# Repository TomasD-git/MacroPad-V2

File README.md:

# MacroPad-V2

A compact 16-key macro pad with rotary encoder and built-in battery — powered by ESP32, fully wireless.  

## Features

- 16 Programmable Keys  
- Rotary Encoder  
- Battery Powered  
- ESP32 with bluetooth  

## How It Works

The MacroPad-V2 uses a seeed xiao ESP32 S3 to manage key matrix and rotary encoder.  

Power is managed by a charging module.  

Firmware handles Bluetooth. The case is 3D printed, with space for the PCB, battery, keys and encoder.  

<details>
  <summary>Pictures</summary>

</details>

<details>
<summary>BOM</summary>

| Name | Purpose | Quantity | Total Cost (USD) | Link | Distributor |
|------|--------|----------|------------------|------|-------------|
| PCB | How would i even make it without PCB | 1 | 11.34 | https://jlcpcb.com | jlcpcb |
| Pin header 2.54mm | soldered onto the pcb then on top of that is the esp32(so it can be visible), the rotary encoder needs this as well | 1 | 3.08 | https://www.aliexpress.com/item/4000873858801.html | Aliepress |
| 1N4148W T4 SOD-123(Diode) | needed in switch matrix(prevents ghosting) | 1 | 2.16 | https://www.aliexpress.com/item/1005010653199938.html | Aliexpress |
| Seeed xiao ESP32 S3 | brain of everything, needed to power use and control all switches and rotary encoder | 1 | 9.06 | https://www.aliexpress.com/item/1005007341749305.html | Aliepress |
| M4 screws 20pcs, 8mm | screwed into heatset inserts to hold case and pcb together | 1 | 2.16 | https://www.aliexpress.com/item/32810872544.html | Aliexpress |
| Heatset inserts, M4 (OD5mm) 30pcs, Length 3mm | Will be melted into the 3D printed case and screws will be inserted into it to hold the case together | 1 | 2.43 | https://www.aliexpress.com/item/1005008666672949.html | Aliexpress |
| Battery holder | Holds battery in place | 1 | 1.84 | https://www.aliexpress.com/item/1005006783038553.html | Aliexpress |
| Battery | to store electricity and later power the esp32 | 1 | 8.85 | https://www.aliexpress.com/item/32810182330.html | Aliexpress |
| Slide switch | shut power to esp32 so it wont consume electricity when not used | 1 | 1.8 | https://www.aliexpress.com/item/1005005633418066.html | Aliexpress |
| Charging module | safely power esp32 and charge battery | 1 | 2.0 | https://www.aliexpress.com/item/1005007176376691.html | Aliexpress |
| Key switches | To use the macropad, (Self sourced) | 1 | 0.0 | https://www.aliexpress.com/item/1005007666734237.html | Aliexpress |
| Rotary encoder | is a part on the pcb | 1 | 1.47 | https://www.aliexpress.com/item/1005009040530746.html | Aliexpress |

</details>

<details>
  <summary>License</summary>

### MIT License

**Copyright (c) [2026] [TomasD-git]**

Permission is hereby granted, free of charge, to any person obtaining a copy
of this software and associated documentation files (the "Software"), to deal
in the Software without restriction, including without limitation the rights
to use, copy, modify, merge, publish, distribute, sublicense, and/or sell
copies of the Software, and to permit persons to whom the Software is
furnished to do so, subject to the following conditions:

The above copyright notice and this permission notice shall be included in all
copies or substantial portions of the Software.

THE SOFTWARE IS PROVIDED "AS IS", WITHOUT WARRANTY OF ANY KIND, EXPRESS OR
IMPLIED, INCLUDING BUT NOT LIMITED TO THE WARRANTIES OF MERCHANTABILITY,
FITNESS FOR A PARTICULAR PURPOSE AND NONINFRINGEMENT. IN NO EVENT SHALL THE
AUTHORS OR COPYRIGHT HOLDERS BE LIABLE FOR ANY CLAIM, DAMAGES OR OTHER
LIABILITY, WHETHER IN AN ACTION OF CONTRACT, TORT OR OTHERWISE, ARISING FROM,
OUT OF OR IN CONNECTION WITH THE SOFTWARE OR THE USE OR OTHER DEALINGS IN THE
SOFTWARE.

</details>

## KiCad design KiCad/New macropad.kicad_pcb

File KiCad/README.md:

# Here you can find all KiCad related files

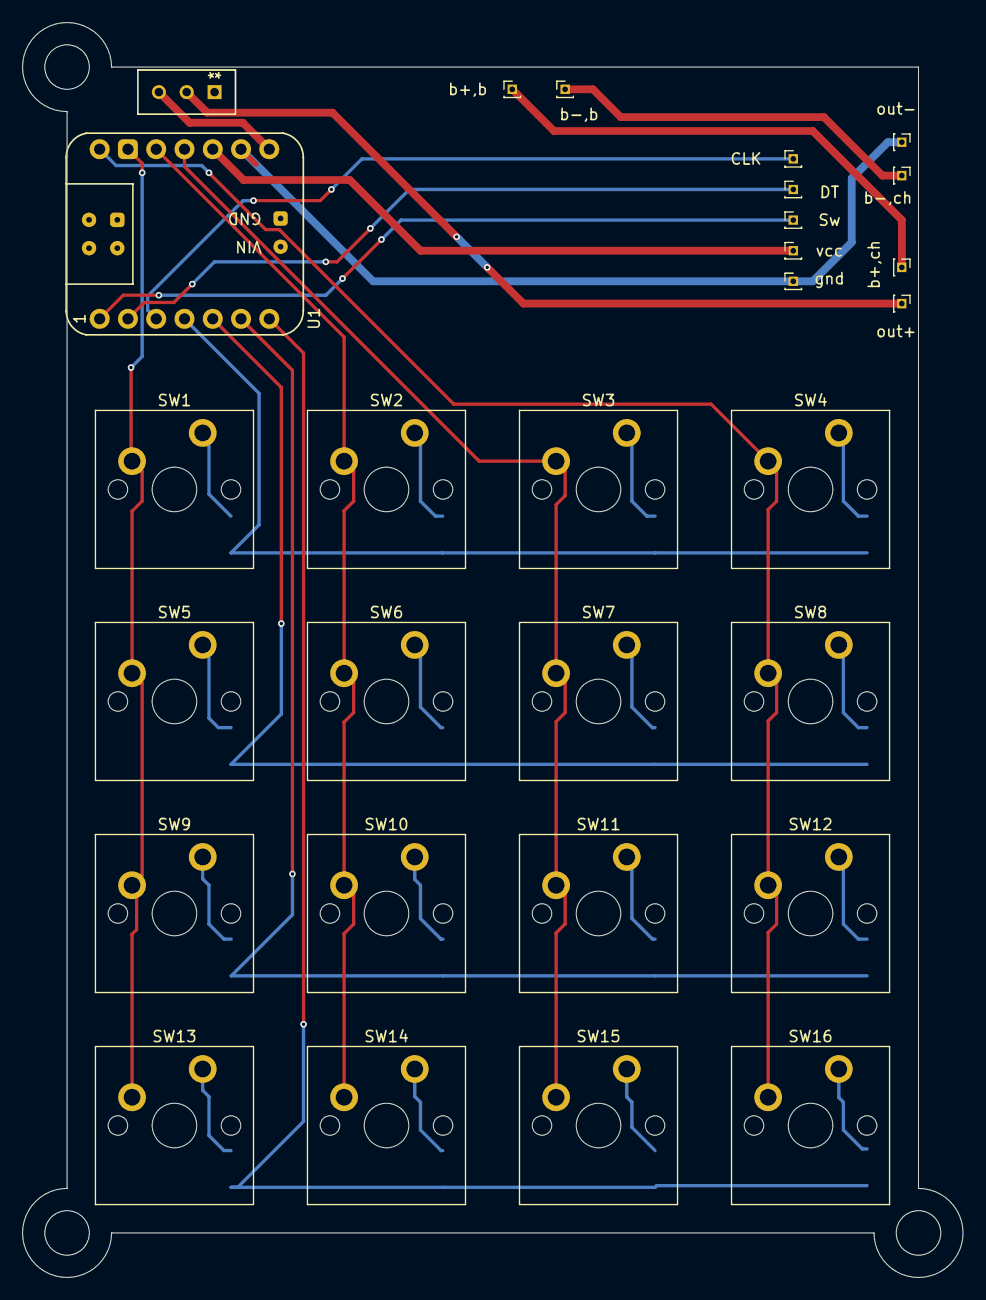
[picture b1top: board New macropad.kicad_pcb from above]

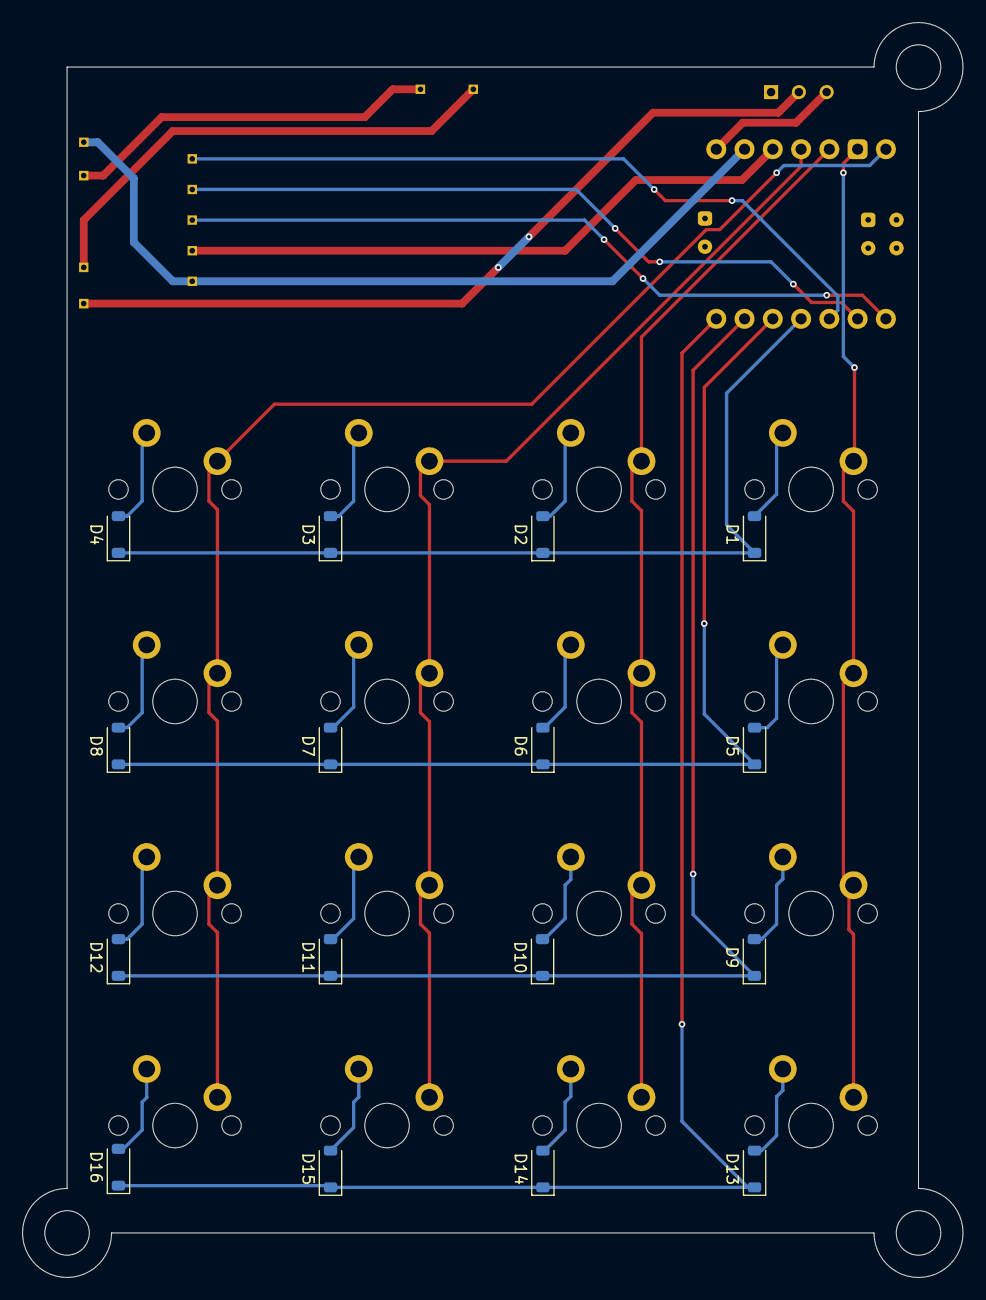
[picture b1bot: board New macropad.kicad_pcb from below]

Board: 2 copper layers, 84.5 x 112.7 mm, 45 parts (16 on the bottom side), 33 nets.

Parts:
CLK: Conn_01x01_Socket; PinHeader_1x01_P1.00mm_Vertical
D1, D2, D3, D4, D5, D6, D7, D8, D9, D10, D11, D12, D13, D14, D15, D16: 1N4148WT; D_SOD-123
DT: Conn_01x01_Socket; PinHeader_1x01_P1.00mm_Vertical
SW1, SW2, SW3, SW4, SW5, SW6, SW7, SW8, SW9, SW10, SW11, SW12, SW13, SW14, SW15, SW16: SW_Push; SW_Cherry_MX_PCB_1.00u
SW17: SS-12D00-G 4 E; 1P2T_SS-12D00_CNK
Sw: Conn_01x01_Socket; PinHeader_1x01_P1.00mm_Vertical
U1: XIAO-ESP32-C3-DIP; Xiao_rp2040_AH_Pogo
b+,b: Conn_01x01_Socket; PinHeader_1x01_P1.00mm_Vertical
b+,ch: Conn_01x01_Socket; PinHeader_1x01_P1.00mm_Vertical
b-,b: Conn_01x01_Socket; PinHeader_1x01_P1.00mm_Vertical
b-,ch: Conn_01x01_Socket; PinHeader_1x01_P1.00mm_Vertical
gnd: Conn_01x01_Socket; PinHeader_1x01_P1.00mm_Vertical
out+: Conn_01x01_Socket; PinHeader_1x01_P1.00mm_Vertical
out-: Conn_01x01_Socket; PinHeader_1x01_P1.00mm_Vertical
vcc: Conn_01x01_Socket; PinHeader_1x01_P1.00mm_Vertical

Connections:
+5V: SW17.3, U1.14 (VBUS)
/Col 1: SW1.1, SW5.1, SW9.1, SW13.1, U1.9 (GPIO8/D8/SCK)
/Col 2: SW2.1, SW6.1, SW10.1, SW14.1, U1.10 (GPIO9/D9/MISO)
/Col 3: SW3.1, SW7.1, SW11.1, SW15.1, U1.11 (GPIO10/D10/MOSI)
/Col 4: SW4.1, SW8.1, SW12.1, SW16.1, U1.8 (GPIO20/D7/RX)
/Row 1: D1.1 (K), D2.1 (K), D3.1 (K), D4.1 (K), U1.4 (GPIO5/A3/D3)
/Row 2: D5.1 (K), D6.1 (K), D7.1 (K), D8.1 (K), U1.5 (GPIO6/D4/SDA)
/Row 3: D9.1 (K), D10.1 (K), D11.1 (K), D12.1 (K), U1.6 (GPIO7/D5/SCL)
/Row 4: D13.1 (K), D14.1 (K), D15.1 (K), D16.1 (K), U1.7 (GPIO21/D6/TX)
GND: U1.13 (GND), gnd.1, out-.1
unnamed: CLK.1, U1.3 (GPIO4/A2/D2)
unnamed: D1.2 (A), SW1.2
unnamed: D2.2 (A), SW2.2
unnamed: D3.2 (A), SW3.2
unnamed: D4.2 (A), SW4.2
unnamed: D5.2 (A), SW5.2
unnamed: D6.2 (A), SW6.2
unnamed: D7.2 (A), SW7.2
unnamed: D8.2 (A), SW8.2
unnamed: D9.2 (A), SW9.2
unnamed: D10.2 (A), SW10.2
unnamed: D11.2 (A), SW11.2
unnamed: D12.2 (A), SW12.2
unnamed: D13.2 (A), SW13.2
unnamed: D14.2 (A), SW14.2
unnamed: D15.2 (A), SW15.2
unnamed: D16.2 (A), SW16.2
unnamed: DT.1, U1.2 (GPIO3/A1/D1)
unnamed: Sw.1, U1.1 (GPIO2/A0/D0)
unnamed: b+,b.1, b+,ch.1
unnamed: b-,b.1, b-,ch.1
unnamed: SW17.2, out+.1
VCC: U1.12 (VCC_3V3), vcc.1

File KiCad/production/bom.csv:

Designator,Footprint,Quantity,Value,LCSC Part #
"B+,B, B+,CH, B-,B, B-,CH, CLK, DT, GND, OUT+, OUT-, SW, VCC",PinHeader_1x01_P1.00mm_Vertical,11,Conn_01x01_Socket,
"D1, D10, D11, D12, D13, D14, D15, D16, D2, D3, D4, D5, D6, D7, D8, D9",D_SOD-123,16,1N4148WT,
"SW1, SW10, SW11, SW12, SW13, SW14, SW15, SW16, SW2, SW3, SW4, SW5, SW6, SW7, SW8, SW9",SW_Cherry_MX_PCB_1.00u,16,SW_Push,
SW17,1P2T_SS-12D00_CNK,1,SS-12D00-G 4 E,
U1,Xiao_rp2040_AH_Pogo,1,XIAO-ESP32-C3-DIP,

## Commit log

2026-04-01 Update README with rotary encoder information
    Added links for rotary encoder and CAD file.
2026-04-02 Add charging module link to README
2026-04-02 Add slide switch link to README
2026-04-02 Add battery and battery holder links to README
2026-04-06 Add heatset inserts to the materials list
2026-04-08 Add initial firmware README file
2026-04-08 added firmware
2026-04-08 Add initial README for CAD files
2026-04-08 Remove outdated component links from README
    Removed outdated links to components in the README.
2026-04-08 added source and full CAD files
2026-04-08 added CAD files
2026-04-08 Add README.md for pictures directory
2026-04-08 Add initial README for KiCad files
2026-04-08 added kicad files
2026-04-08 Enhance README with features and usage details
    Expanded README to include features, usage details, and licensing information.
2026-04-22 added BOM
2026-04-22 added gerber file
